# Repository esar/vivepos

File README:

This repository contains the PCB design and firmware for
a stanalone position sensor for use with the VIVE VR system.

 * 4 sensors, 30 positions/s each
 * Totally standalone, works out lighthouse positions for itself
 * No configuration, apply power... get position data
 * Accounts for gravity direction using accelerometer data from lighthouses
 * Output sent via USB serial and/or UART
 * Running on a 20MHz AVR

For latest version and full description, go to:
http://hacks.esar.org.uk/vive-position-sensor/

How to use:

1) Manufacture the board that can be found in the 'board' directory 
   (CADSoft Eagle format).
2) Edit Makefile and change paths to tools:
   CCDEVS, CCINC, CC, OBJCOPY, OBJDUMP
3) Run 'make' to build the firmware
4) Write firmware to board, e.g.:
   avrdude -c jtag2updi -P /dev/ttyACM1 -p m3209 -U flash:w:image.hex
5) Connect USB (or power+UART) to board
6) The board should start outputing position data shortly after
   the lighthouses become visible to it.
7) Use the solve-lighthouse.py script to pretty print the data stream:
   ./solve-lighthouse.py --dump-pos --dump-sensor=0 /dev/ttyACM0

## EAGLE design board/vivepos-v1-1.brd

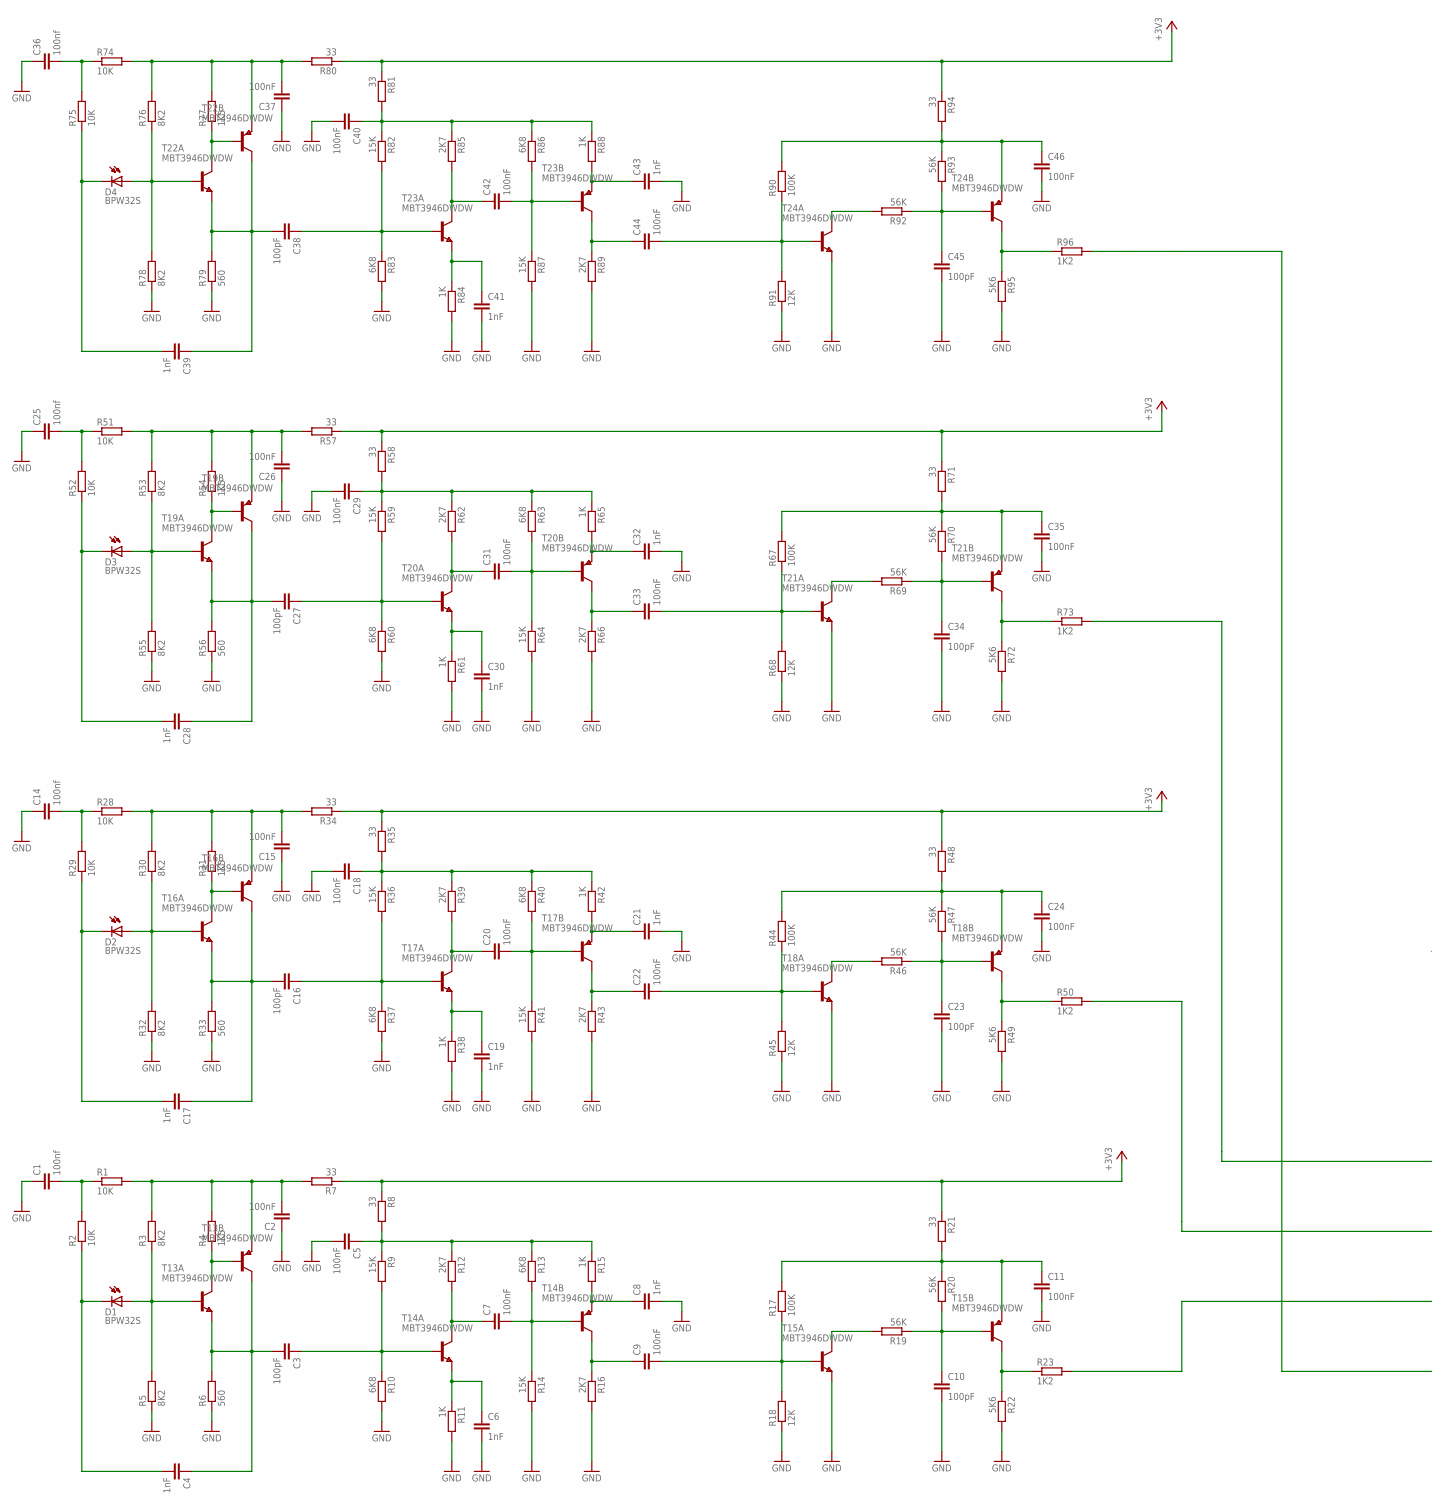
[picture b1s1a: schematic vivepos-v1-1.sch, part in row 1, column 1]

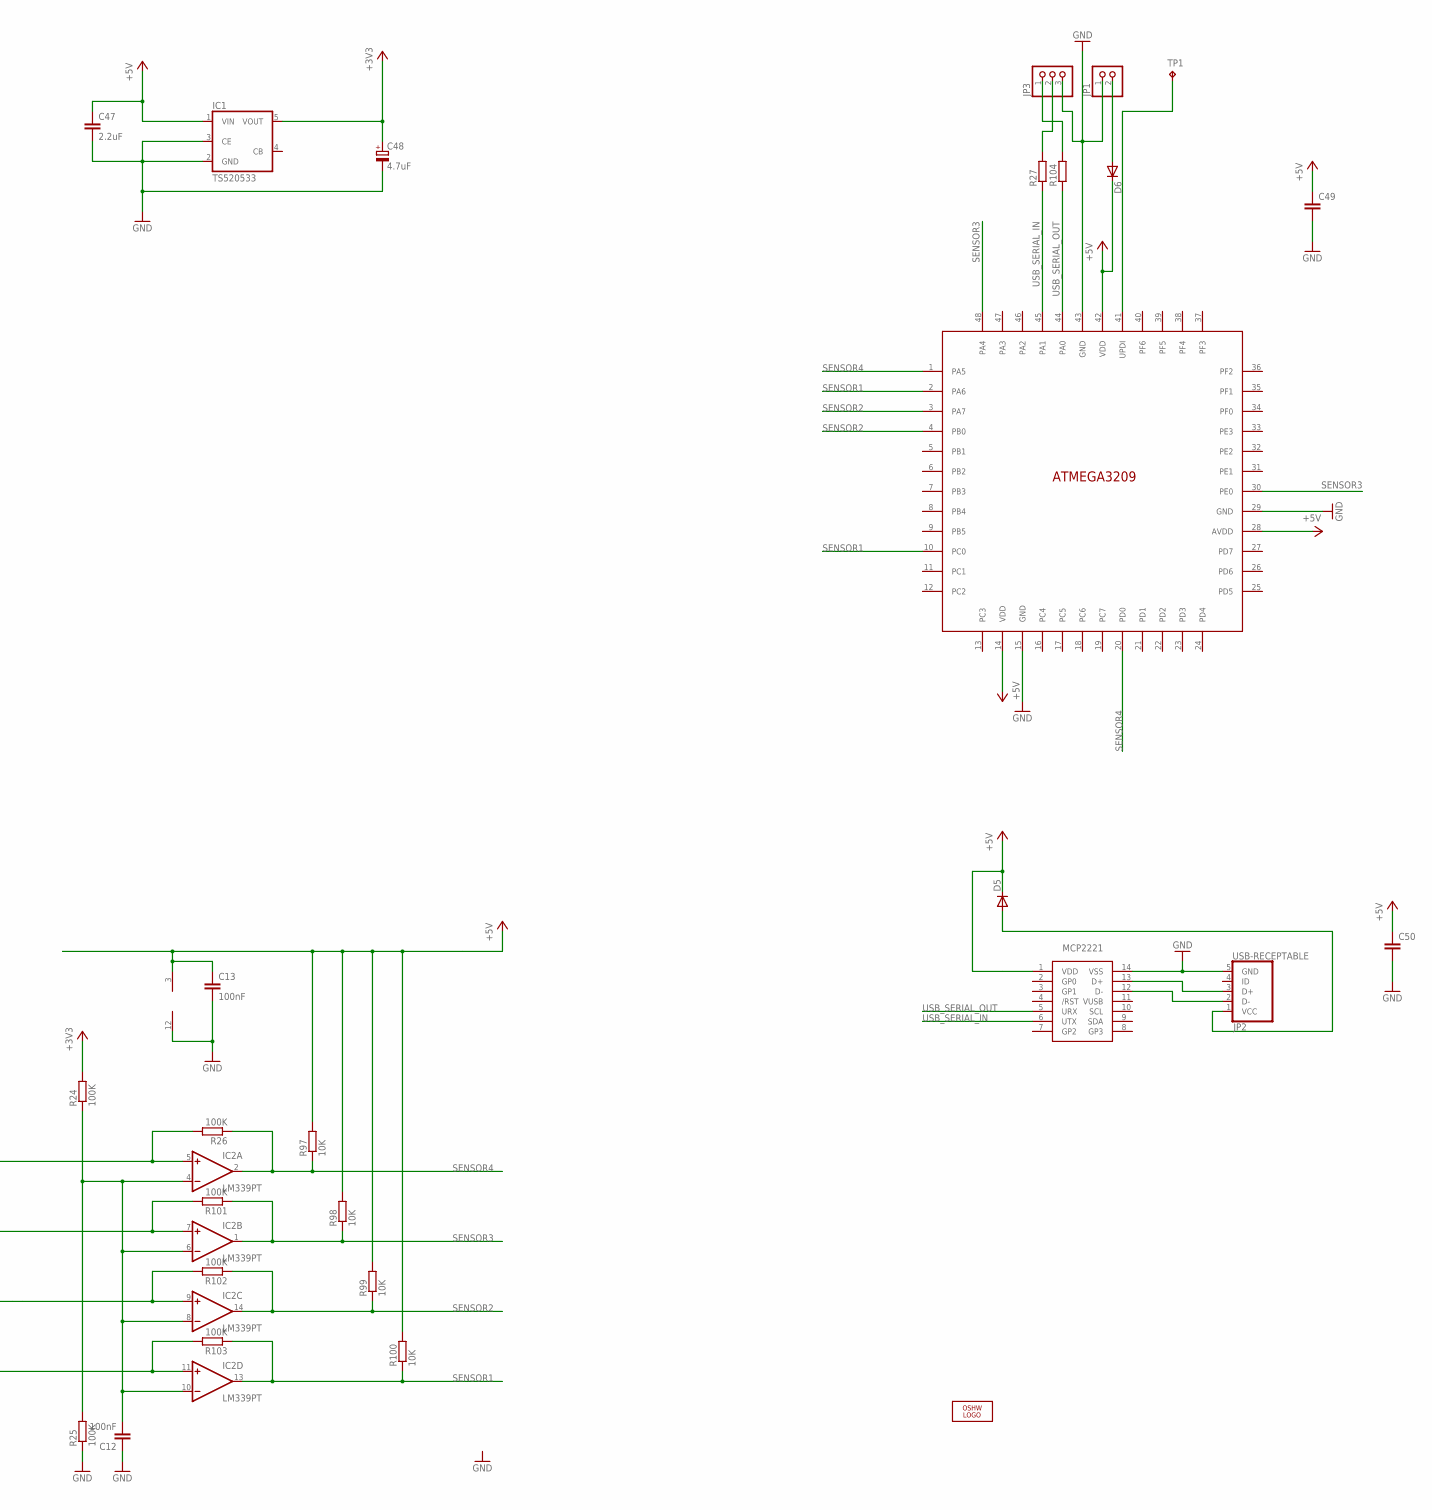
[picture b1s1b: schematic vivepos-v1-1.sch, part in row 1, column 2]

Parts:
C1, C14, C25, C36: 100nf; C0402
C2, C5, C7, C9, C11, C12, C13, C15, C18, C20, C22, C24, C26, C29, C31, C33, C35, C37, C40, C42, C44, C46: 100nF; C0402
C3, C10, C16, C23, C27, C34, C38, C45: 100pF; C0402
C4, C6, C8, C17, C19, C21, C28, C30, C32, C39, C41, C43: 1nF; C0402
C47: 2.2uF; C0805
C48: 4.7uF; B/3528-21R
C49: C-EUC0402; C0402
C50: C-EUC0603; C0603
D1, D2, D3, D4: BPW32S; BPW34S
D5, D6: DIODE-SOD323-W; SOD323-W
IC1: TS520533; SOT25
IC2: LM339PT; TSSOP14
JP1: PINHD-1X2; 1X02
JP2: USB-RECEPTABLE; FCI-10103594-0001LF
JP3: PINHD-1X3; 1X03
LOGO1: OSHW_LOGO_FILLX0200-NT; OSHW_FILLX200_NOTEXT
R1, R2, R28, R29, R51, R52, R74, R75, R97, R98, R99, R100: 10K; R0402
R3, R5, R30, R32, R53, R55, R76, R78: 8K2; R0402
R4, R31, R54, R77: 1K5; R0402
R6, R33, R56, R79: 560; R0402
R7, R8, R21, R34, R35, R48, R57, R58, R71, R80, R81, R94: 33; R0402
R9, R14, R36, R41, R59, R64, R82, R87: 15K; R0402
R10, R13, R37, R40, R60, R63, R83, R86: 6K8; R0402
R11, R15, R38, R42, R61, R65, R84, R88: 1K; R0402
R12, R16, R39, R43, R62, R66, R85, R89: 2K7; R0402
R17, R24, R25, R26, R44, R67, R90, R101, R102, R103: 100K; R0402
R18, R45, R68, R91: 12K; R0402
R19, R20, R46, R47, R69, R70, R92, R93: 56K; R0402
R22, R49, R72, R95: 5K6; R0402
R23, R50, R73, R96: 1K2; R0402
R27, R104: R-EU_R0402; R0402
T13, T14, T15, T16, T17, T18, T19, T20, T21, T22, T23, T24: MBT3946DWDW; SOT363_PHILIPS
TP1: TPTP15R; TP15R
U$1: MCP2221; SOIC14
U$2: ATMEGA3209; TQFP48

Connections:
+3V3: C48.+, IC1.5 (VOUT), R7.1, R8.1, R21.1, R24.2, R34.1, R35.1, R48.1, R57.1, R58.1, R71.1, R80.1, R81.1, R94.1
+5V: C13.1, C47.1, C49.1, C50.1, D5.C, D6.C, IC1.1 (VIN), IC2.3 (V+), R97.2, R98.2, R99.2, R100.2, U$1.1 (VDD), U$2.14 (VDD), U$2.28 (AVDD), U$2.42 (VDD)
GND: C1.1, C2.1, C5.2, C6.2, C8.2, C10.2, C11.2, C12.1, C13.2, C14.1, C15.1, C18.2, C19.2, C21.2, C23.2, C24.2, C25.1, C26.1, C29.2, C30.2, C32.2, C34.2, C35.2, C36.1, C37.1, C40.2, C41.2, C43.2, C45.2, C46.2, C47.2, C48.-, C49.2, C50.2, IC1.2 (GND), IC1.3 (CE), IC2.12 (GND), JP1.1, JP2.5 (GND), JP3.3, R5.1, R6.1, R10.2, R11.2, R14.2, R16.2, R18.1, R22.2, R25.1, R32.1, R33.1, R37.2, R38.2, R41.2, R43.2, R45.1, R49.2, R55.1, R56.1, R60.2, R61.2, R64.2, R66.2, R68.1, R72.2, R78.1, R79.1, R83.2, R84.2, R87.2, R89.2, R91.1, R95.2, T15.1 (E), T18.1 (E), T21.1 (E), T24.1 (E), U$1.14 (VSS), U$2.15 (GND), U$2.29 (GND), U$2.43 (GND)
unnamed: C1.2, R1.1, R2.2
unnamed: C2.2, R1.2, R3.2, R4.2, R7.2, T13.4 (E)
unnamed: R4.1, T13.5 (B), T13.6 (C)
unnamed: D1.A, R3.1, R5.2, T13.2 (B)
unnamed: C3.2, C4.1, R6.2, T13.1 (E), T13.3 (C)
unnamed: C5.1, R8.2, R9.1, R12.1, R13.1, R15.1
unnamed: C3.1, R9.2, R10.1, T14.2 (B)
unnamed: C7.1, R12.2, T14.6 (C)
unnamed: C6.1, R11.1, T14.1 (E)
unnamed: C8.1, R15.2, T14.4 (E)
unnamed: C7.2, R13.2, R14.1, T14.5 (B)
unnamed: C9.1, R16.1, T14.3 (C)
unnamed: C4.2, D1.K (C), R2.1
unnamed: C9.2, R17.1, R18.2, T15.2 (B)
unnamed: C11.1, R17.2, R20.1, R21.2, T15.4 (E)
unnamed: C10.1, R19.1, R20.2, T15.5 (B)
unnamed: R19.2, T15.6 (C)
unnamed: R22.1, R23.1, T15.3 (C)
unnamed: IC2.9 (+IN), R23.2, R102.2
unnamed: C12.2, IC2.4 (-IN), IC2.6 (-IN), IC2.8 (-IN), IC2.10 (-IN), R24.1, R25.2
unnamed: C14.2, R28.1, R29.2
unnamed: D6.A, JP1.2
unnamed: C15.2, R28.2, R30.2, R31.2, R34.2, T16.4 (E)
unnamed: R31.1, T16.5 (B), T16.6 (C)
unnamed: D2.A, R30.1, R32.2, T16.2 (B)
unnamed: C16.2, C17.1, R33.2, T16.1 (E), T16.3 (C)
unnamed: D5.A, JP2.1 (VCC)
unnamed: C18.1, R35.2, R36.1, R39.1, R40.1, R42.1
unnamed: C16.1, R36.2, R37.1, T17.2 (B)
unnamed: C20.1, R39.2, T17.6 (C)
unnamed: C19.1, R38.1, T17.1 (E)
unnamed: C20.2, R40.2, R41.1, T17.5 (B)
unnamed: C21.1, R42.2, T17.4 (E)
unnamed: C22.1, R43.1, T17.3 (C)
unnamed: C17.2, D2.K (C), R29.1
unnamed: C22.2, R44.1, R45.2, T18.2 (B)
unnamed: C24.1, R44.2, R47.1, R48.2, T18.4 (E)
unnamed: C23.1, R46.1, R47.2, T18.5 (B)
unnamed: R46.2, T18.6 (C)
unnamed: R49.1, R50.1, T18.3 (C)
unnamed: C25.2, R51.1, R52.2
unnamed: C26.2, R51.2, R53.2, R54.2, R57.2, T19.4 (E)
unnamed: R54.1, T19.5 (B), T19.6 (C)
unnamed: D3.A, R53.1, R55.2, T19.2 (B)
unnamed: C27.2, C28.1, R56.2, T19.1 (E), T19.3 (C)
unnamed: TP1.TP, U$2.41 (UPDI)
unnamed: C29.1, R58.2, R59.1, R62.1, R63.1, R65.1
unnamed: C27.1, R59.2, R60.1, T20.2 (B)
unnamed: C31.1, R62.2, T20.6 (C)
unnamed: C30.1, R61.1, T20.1 (E)
unnamed: C31.2, R63.2, R64.1, T20.5 (B)
unnamed: C32.1, R65.2, T20.4 (E)
unnamed: C33.1, R66.1, T20.3 (C)
unnamed: C28.2, D3.K (C), R52.1
unnamed: C33.2, R67.1, R68.2, T21.2 (B)
unnamed: C35.1, R67.2, R70.1, R71.2, T21.4 (E)
unnamed: C34.1, R69.1, R70.2, T21.5 (B)
unnamed: R69.2, T21.6 (C)
unnamed: R72.1, R73.1, T21.3 (C)
unnamed: JP3.2, R27.2
unnamed: C36.2, R74.1, R75.2
unnamed: C37.2, R74.2, R76.2, R77.2, R80.2, T22.4 (E)
unnamed: R77.1, T22.5 (B), T22.6 (C)
unnamed: D4.A, R76.1, R78.2, T22.2 (B)
unnamed: C38.2, C39.1, R79.2, T22.1 (E), T22.3 (C)
unnamed: JP3.1, R104.2
unnamed: C40.1, R81.2, R82.1, R85.1, R86.1, R88.1
unnamed: C38.1, R82.2, R83.1, T23.2 (B)
unnamed: C42.1, R85.2, T23.6 (C)
unnamed: C41.1, R84.1, T23.1 (E)
unnamed: C42.2, R86.2, R87.1, T23.5 (B)
unnamed: C43.1, R88.2, T23.4 (E)
unnamed: C44.1, R89.1, T23.3 (C)
unnamed: C39.2, D4.K (C), R75.1
unnamed: C44.2, R90.1, R91.2, T24.2 (B)
unnamed: C46.1, R90.2, R93.1, R94.2, T24.4 (E)
unnamed: C45.1, R92.1, R93.2, T24.5 (B)
unnamed: R92.2, T24.6 (C)
unnamed: R95.1, R96.1, T24.3 (C)
unnamed: JP2.3 (D+), U$1.13 (D+)
unnamed: JP2.2 (D-), U$1.12 (D-)
unnamed: IC2.7 (+IN), R50.2, R101.2
unnamed: IC2.11 (+IN), R96.2, R103.2
unnamed: IC2.5 (+IN), R26.2, R73.2
SENSOR1: IC2.13 (OUT), R100.1, R103.1, U$2.2 (PA6), U$2.10 (PC0)
SENSOR2: IC2.14 (OUT), R99.1, R102.1, U$2.3 (PA7), U$2.4 (PB0)
SENSOR3: IC2.1 (OUT), R98.1, R101.1, U$2.30 (PE0), U$2.48 (PA4)
SENSOR4: IC2.2 (OUT), R26.1, R97.1, U$2.1 (PA5), U$2.20 (PD0)
USB_SERIAL_IN: R27.1, U$1.6 (UTX), U$2.45 (PA1)
USB_SERIAL_OUT: R104.1, U$1.5 (URX), U$2.44 (PA0)

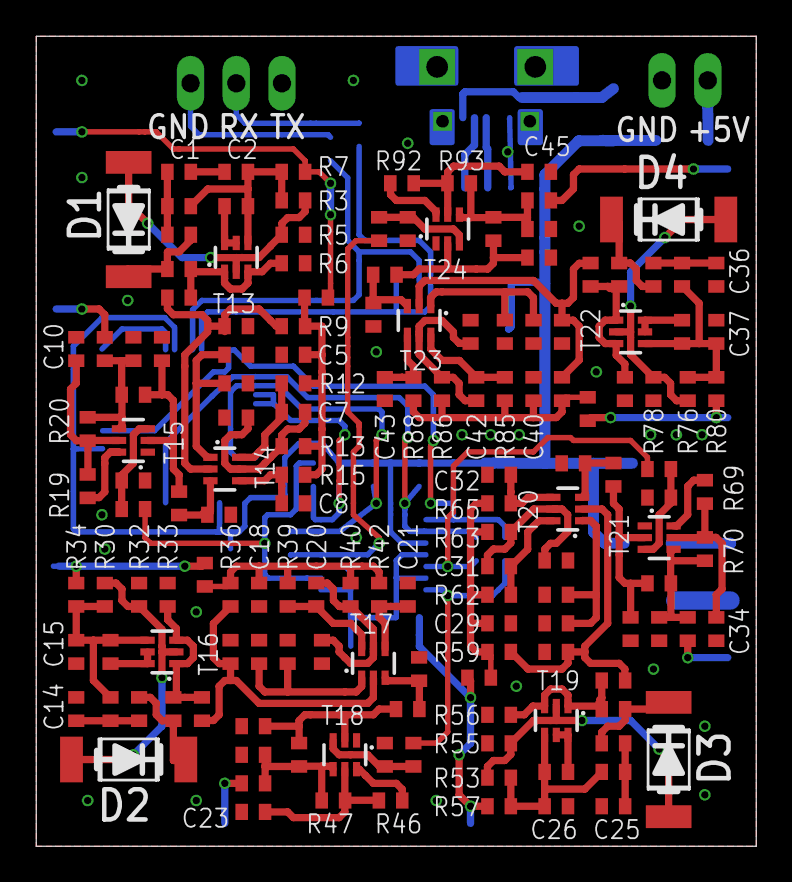
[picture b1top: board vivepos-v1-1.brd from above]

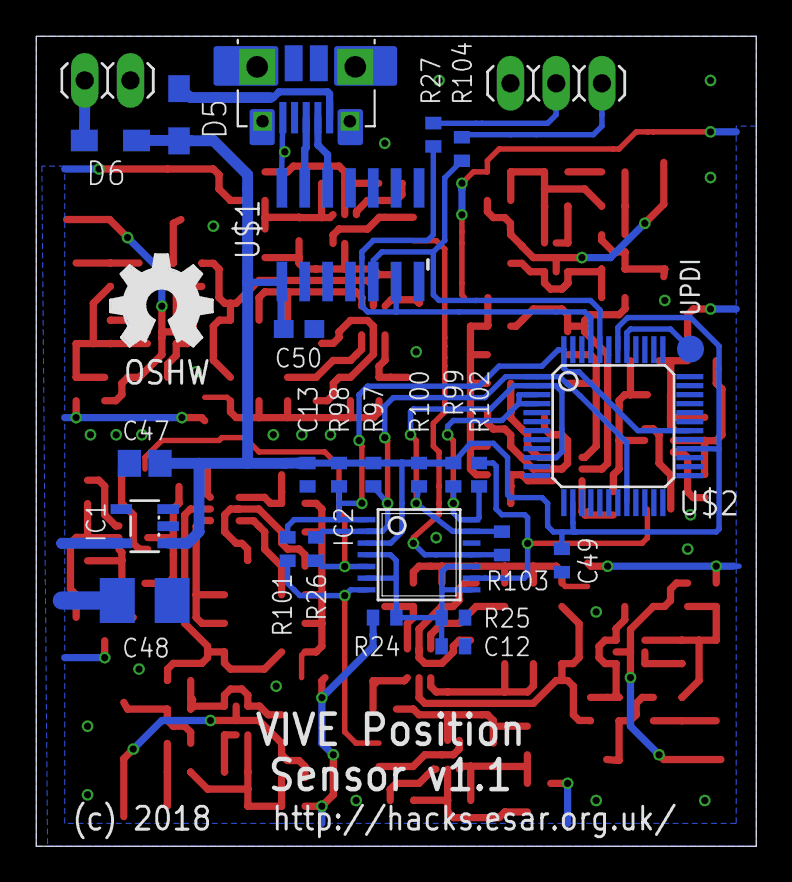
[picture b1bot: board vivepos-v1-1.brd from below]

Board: 2 copper layers, 40.0 x 45.0 mm, 181 parts (29 on the bottom side), 93 nets.

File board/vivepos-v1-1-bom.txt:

Resistors (all 1% 0402 SMD)
===========================
33R        R7,R8,R21,R34,R35,R48,R57,R58,R71,R80,R81,R94
560R       R6,R33,R56,R79
100K       R17,R24,R25,R26,R44,R67,R90,R101,R102,R103
10K        R1,R2,R28,R29,R51,R52,R74,R75,R97,R98,R99,R100
12K        R18,R45,R68,R91
15K        R9,R14,R36,R41,R59,R64,R82,R87
1K         R11,R15,R27,R38,R42,R61,R65,R84,R88,R104
1K2        R23,R50,R73,R96
1K5        R4,R31,R54,R77
2K7        R12,R16,R39,R43,R62,R66,R85,R89
56K        R19,R20,R46,R47,R69,R70,R92,R93
5K6        R22,R49,R72,R95
6K8        R10,R13,R37,R40,R60,R63,R83,R86
8K2        R3,R5,R30,R32,R53,R55,R76,R78

Capacitors (Ceramic 0402 SMD)
=====================
100nF      C1,C2,C5,C7,C9,C11,C12,C13,C14,C15,C18,C20,C22,C24,C25,C26,C29,C31,C33,C35,C36,C37,C40,C42,C44,C46
100pF      C3,C10,C16,C23,C27,C34,C38,C45
1nF        C4,C6,C8,C17,C19,C21,C28,C30,C32,C39,C41,C43,C49,C50

Capacitors (other)
=================
2.2uF    Ceramic 0805                                                     C47
4.7uF    16V Tantalum (Kemet B45196E3475K209, no longer manufactured)     C48

Diodes
======
Photo-diode BPW32S             D1,D2,D3,D4
Schottky    PMEG3010EJ.115     D5,D6

Semiconductors
==============
Microcontroller ATMEGA3209     U$2
Quad Comparator LM339PT        IC2
Dual NPN/PNP    MBT3946DWDW    T13,T14,T15,T16,T17,T18,T19,T20,T21,T22,T23,T24
USB Serial      MCP2221        U$1
3V3 regulator   TPS76933DBVT   IC1

Connectors
==========
PINHD-1X2                     JP1
PINHD-1X3                     JP3
USB Amphenol 10103594-0001LF  JP2

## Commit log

2018-08-28 sped up decodeWidth, average latest angle with last
2018-08-30 added OOTX data decode
2018-08-31 handle both lighthouses
2018-09-06 ensure rising edges are processed before falling edges
2018-09-06 separate OOTX buffers for each sensor and each lighthouse
2018-09-06 don't block in printf
2018-09-14 add python script to find lighthouse locations
2018-09-14 solve-lighthouse.py: fix constant names
2018-09-16 swap debug timeout printf for pin toggle
2018-09-16 Fix processing window comment
2018-09-16 fix cos/sin in solve-lighthouse.py after removing sympy import
2018-09-16 rotate lighthouse solution for gravity
2018-10-14 Implement lighthouse position solver on microcontroller
2018-12-28 update code for v1.1 board
2018-12-28 Make initial lighthouse solution calculation more reliable
2018-12-28 Add missing total error calculation
2018-12-29 Detect and fix bad lighthouse solutions (lighthouse below sensor plane, sensor plane behind lighthouse)
2018-12-31 Added PCB to repo
2018-12-31 Added BOM
2018-12-31 Added license info
2018-12-31 Added README

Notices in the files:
board/vivepos-v1-1.brd:
(c) 2018
